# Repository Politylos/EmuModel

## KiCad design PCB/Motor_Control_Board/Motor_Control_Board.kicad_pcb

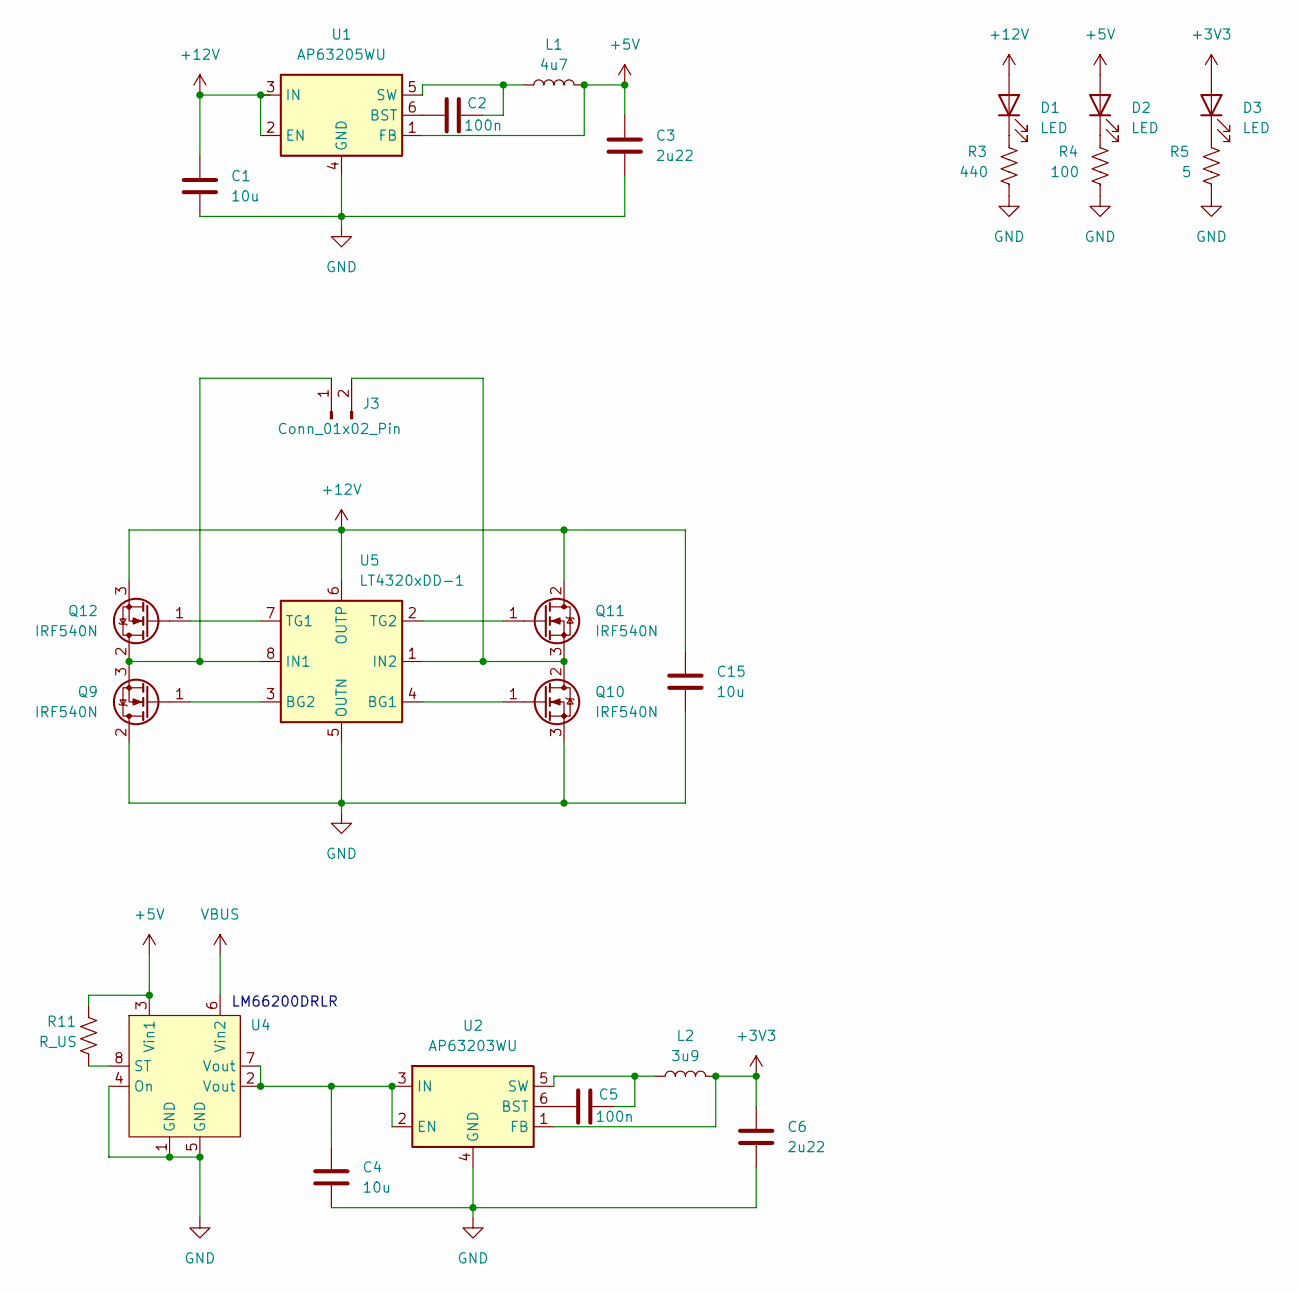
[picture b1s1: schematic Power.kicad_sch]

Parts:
C1, C4, C15: 10u; C_1206_3216Metric_Pad1.33x1.80mm_HandSolder
C2, C5: 100n; C_1206_3216Metric_Pad1.33x1.80mm_HandSolder
C3, C6: 2u22; C_1206_3216Metric_Pad1.33x1.80mm_HandSolder
D1, D2, D3: LED; LED_1206_3216Metric_Pad1.42x1.75mm_HandSolder; MPN 150120GS75000
J3: Conn_01x02_Pin; PinHeader_1x02_P1.27mm_Vertical
L1: 4u7; L_1206_3216Metric_Pad1.42x1.75mm_HandSolder
L2: 3u9; L_1206_3216Metric_Pad1.42x1.75mm_HandSolder
Q9, Q10, Q11, Q12: IRF540N; SOT-23-3
R3: 440; R_1206_3216Metric_Pad1.30x1.75mm_HandSolder
R4: 100; R_1206_3216Metric_Pad1.30x1.75mm_HandSolder
R5: 5; R_1206_3216Metric_Pad1.30x1.75mm_HandSolder
R11: R_US; R_1206_3216Metric_Pad1.30x1.75mm_HandSolder
U1: AP63205WU; TSOT-23-6
U2: AP63203WU; TSOT-23-6
U4: SOT-583-8
U5: LT4320xDD-1; DFN-8-1EP_3x3mm_P0.5mm_EP1.65x2.38mm

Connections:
+3V3: C6.1, D3.2 (A), L2.2, U2.1 (FB); also elsewhere on the board
+5V: C3.1, D2.2 (A), L1.2, R11.1, U1.1 (FB), U4.3 (Vin1)
+12V: C1.1, C15.1, D1.2 (A), Q11.2 (D), Q12.3 (S), U1.2 (EN), U1.3 (IN), U5.6 (OUTP); also elsewhere on the board
GND: C1.2, C3.2, C4.2, C6.2, C15.2, Q9.2 (D), Q10.3 (S), R3.2, R4.2, R5.2, U1.4 (GND), U2.4 (GND), U4.1 (GND), U4.4 (On), U4.5 (GND), U5.5 (OUTN), U5.9 (OUTN); also elsewhere on the board
unnamed: D1.1 (K), R3.1
unnamed: D2.1 (K), R4.1
unnamed: D3.1 (K), R5.1
unnamed: J3.1, Q9.3 (S), Q12.2 (D), U5.8 (IN1)
unnamed: J3.2, Q10.2 (D), Q11.3 (S), U5.1 (IN2)
unnamed: Q9.1 (G), U5.3 (BG2)
unnamed: Q10.1 (G), U5.4 (BG1)
unnamed: Q11.1 (G), U5.2 (TG2)
unnamed: Q12.1 (G), U5.7 (TG1)
unnamed: C2.1, U1.6 (BST)
unnamed: C2.2, L1.1, U1.5 (SW)
unnamed: C5.1, U2.6 (BST)
unnamed: C4.1, U2.2 (EN), U2.3 (IN), U4.2 (Vout), U4.7 (Vout)
unnamed: C5.2, L2.1, U2.5 (SW)
unnamed: R11.2, U4.8 (ST)
VBUS: U4.6 (Vin2); also elsewhere on the board

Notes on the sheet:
LM66200DRLR

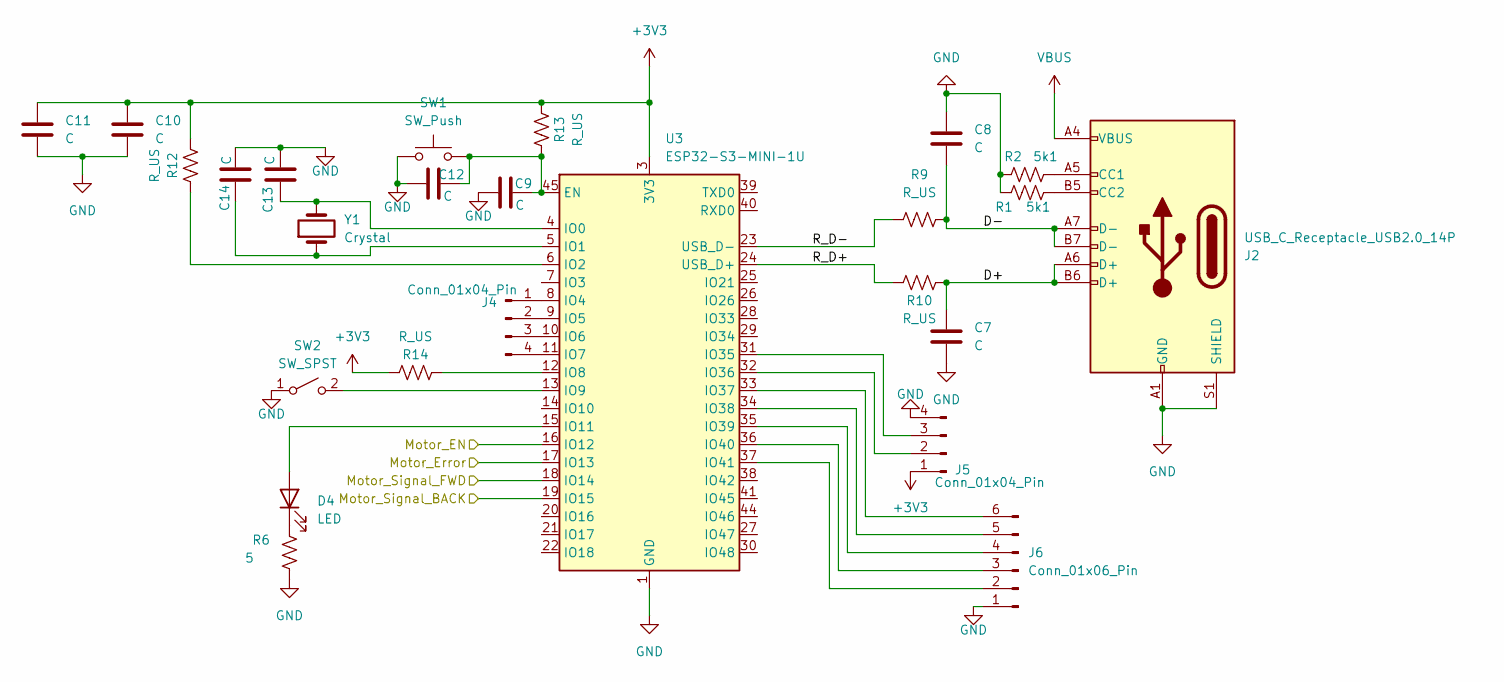
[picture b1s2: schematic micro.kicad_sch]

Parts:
C7, C8, C9, C10, C11, C12, C13, C14: C; C_1206_3216Metric_Pad1.33x1.80mm_HandSolder
D4: LED; LED_1206_3216Metric_Pad1.42x1.75mm_HandSolder; MPN 150120BS75000
J2: USB_C_Receptacle_USB2.0_14P; 216989-0001_MOL
J4, J5: Conn_01x04_Pin; PinHeader_1x04_P1.27mm_Vertical
J6: Conn_01x06_Pin; PinHeader_1x06_P1.27mm_Vertical
R1, R2: 5k1; R_1206_3216Metric_Pad1.30x1.75mm_HandSolder
R6: 5; R_1206_3216Metric_Pad1.30x1.75mm_HandSolder
R9, R10, R12, R13, R14: R_US; R_1206_3216Metric_Pad1.30x1.75mm_HandSolder
SW1: SW_Push; SW_Tactile_SPST_NO_Straight_CK_PTS636Sx25SMTRLFS
SW2: SW_SPST; SW_DIP_SPSTx01_Slide_6.7x4.1mm_W6.73mm_P2.54mm_LowProfile_J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
U3: ESP32-S3-MINI-1U; ESP32-S2-MINI-1U
Y1: Crystal; Oscillator_SMD_Abracon_ASCO-4Pin_1.6x1.2mm

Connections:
+3V3: C10.1, C11.1, J5.1, R12.1, R13.2, R14.2, U3.3 (3V3); also elsewhere on the board
/Motor Controller/Motor_EN: U3.16 (IO12); also elsewhere on the board
/Motor Controller/Motor_Error: U3.17 (IO13); also elsewhere on the board
/Motor Controller/Motor_Signal_BACK: U3.19 (IO15); also elsewhere on the board
/Motor Controller/Motor_Signal_FWD: U3.18 (IO14); also elsewhere on the board
/micro/D+: C7.1, J2.A6 (D+), J2.B6 (D+), R10.2
/micro/D-: C8.2, J2.A7 (D-), J2.B7 (D-), R9.2
/micro/R_D+: R10.1, U3.24 (USB_D+)
/micro/R_D-: R9.1, U3.23 (USB_D-)
GND: C7.2, C8.1, C9.1, C10.2, C11.2, C12.1, C13.1, C14.1, J2.A1 (GND), J2.A12 (GND), J2.B1 (GND), J2.B12 (GND), J2.S1 (SHIELD), J5.4, J6.1, R1.1, R2.1, R6.2, SW1.1, SW2.1 (A), U3.1 (GND), U3.2 (GND), U3.42 (GND), U3.43 (GND), U3.46 (GND), U3.47 (GND), U3.48 (GND), U3.49 (GND), U3.50 (GND), U3.51 (GND), U3.52 (GND), U3.53 (GND), U3.54 (GND), U3.55 (GND), U3.56 (GND), U3.57 (GND), U3.58 (GND), U3.59 (GND), U3.60 (GND), U3.61 (GND), U3.62 (GND), U3.63 (GND), U3.64 (GND), U3.65 (GND); also elsewhere on the board
unnamed: D4.2 (A), U3.15 (IO11)
unnamed: D4.1 (K), R6.1
unnamed: J2.A5 (CC1), R2.2
unnamed: J2.B5 (CC2), R1.2
unnamed: J4.1, U3.8 (IO4)
unnamed: J4.2, U3.9 (IO5)
unnamed: J4.3, U3.10 (IO6)
unnamed: J4.4, U3.11 (IO7)
unnamed: J5.2, U3.32 (IO36)
unnamed: J5.3, U3.31 (IO35)
unnamed: J6.2, U3.37 (IO41)
unnamed: J6.3, U3.36 (IO40)
unnamed: J6.4, U3.35 (IO39)
unnamed: J6.5, U3.34 (IO38)
unnamed: J6.6, U3.33 (IO37)
unnamed: SW2.2 (B), U3.13 (IO9)
unnamed: C9.2, C12.2, R13.1, SW1.2, U3.45 (EN)
unnamed: C13.2, U3.4 (IO0), Y1.2
unnamed: C14.2, U3.5 (IO1), Y1.1
unnamed: R12.2, U3.6 (IO2)
unnamed: R14.1, U3.12 (IO8)
VBUS: J2.A4 (VBUS), J2.A9 (VBUS), J2.B4 (VBUS), J2.B9 (VBUS); also elsewhere on the board

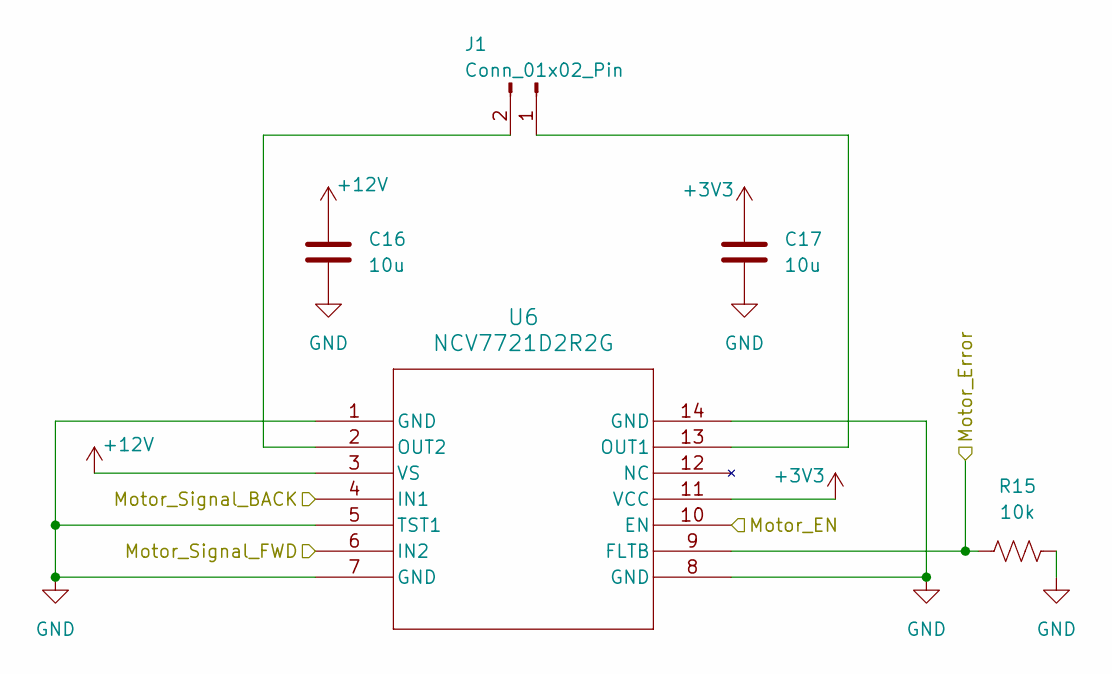
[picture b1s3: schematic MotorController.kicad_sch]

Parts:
C16, C17: 10u; C_1206_3216Metric_Pad1.33x1.80mm_HandSolder
J1: Conn_01x02_Pin; PinHeader_1x02_P1.27mm_Vertical
R15: 10k; R_1206_3216Metric_Pad1.30x1.75mm_HandSolder
U6: NCV7721D2R2G; SOIC14_4X8P75_ONS-L

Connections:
+3V3: C17.1, U6.11 (VCC); also elsewhere on the board
+12V: C16.1, U6.3 (VS); also elsewhere on the board
/Motor Controller/Motor_EN: U6.10 (EN); also elsewhere on the board
/Motor Controller/Motor_Error: R15.1, U6.9 (FLTB); also elsewhere on the board
/Motor Controller/Motor_Signal_BACK: U6.4 (IN1); also elsewhere on the board
/Motor Controller/Motor_Signal_FWD: U6.6 (IN2); also elsewhere on the board
GND: C16.2, C17.2, R15.2, U6.1 (GND), U6.5 (TST1), U6.7 (GND), U6.8 (GND), U6.14 (GND); also elsewhere on the board
unnamed: J1.1, U6.13 (OUT1)
unnamed: J1.2, U6.2 (OUT2)

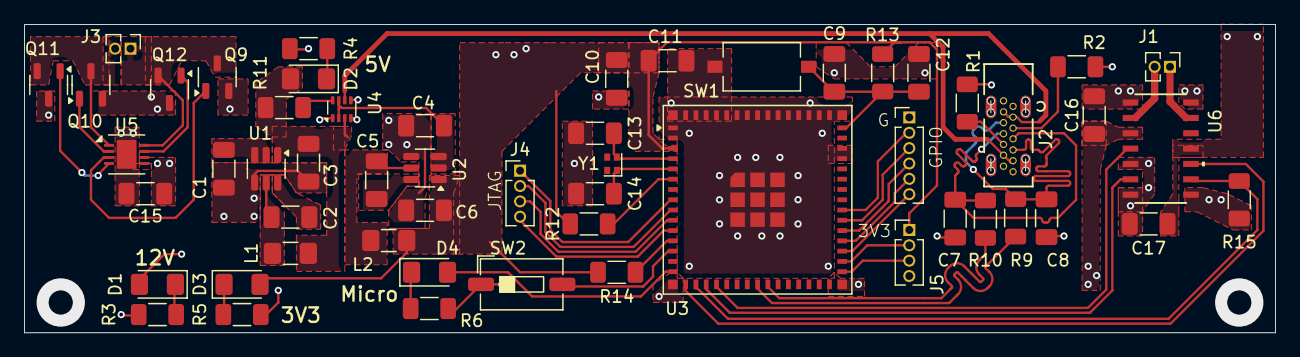
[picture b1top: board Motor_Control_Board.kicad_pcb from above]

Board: 2 copper layers, 103.5 x 25.5 mm, 55 parts (0 on the bottom side), 51 nets.

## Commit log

2025-11-13 rebase commit
2025-11-13 added in PCB and folder struct
